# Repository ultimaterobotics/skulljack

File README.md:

# skulljack
This is a non-contact, open source EEG headset. Project just went public, it isn't properly described and documented yet (although we already have a working prototype). Proper description, firmware and PC source code coming soon

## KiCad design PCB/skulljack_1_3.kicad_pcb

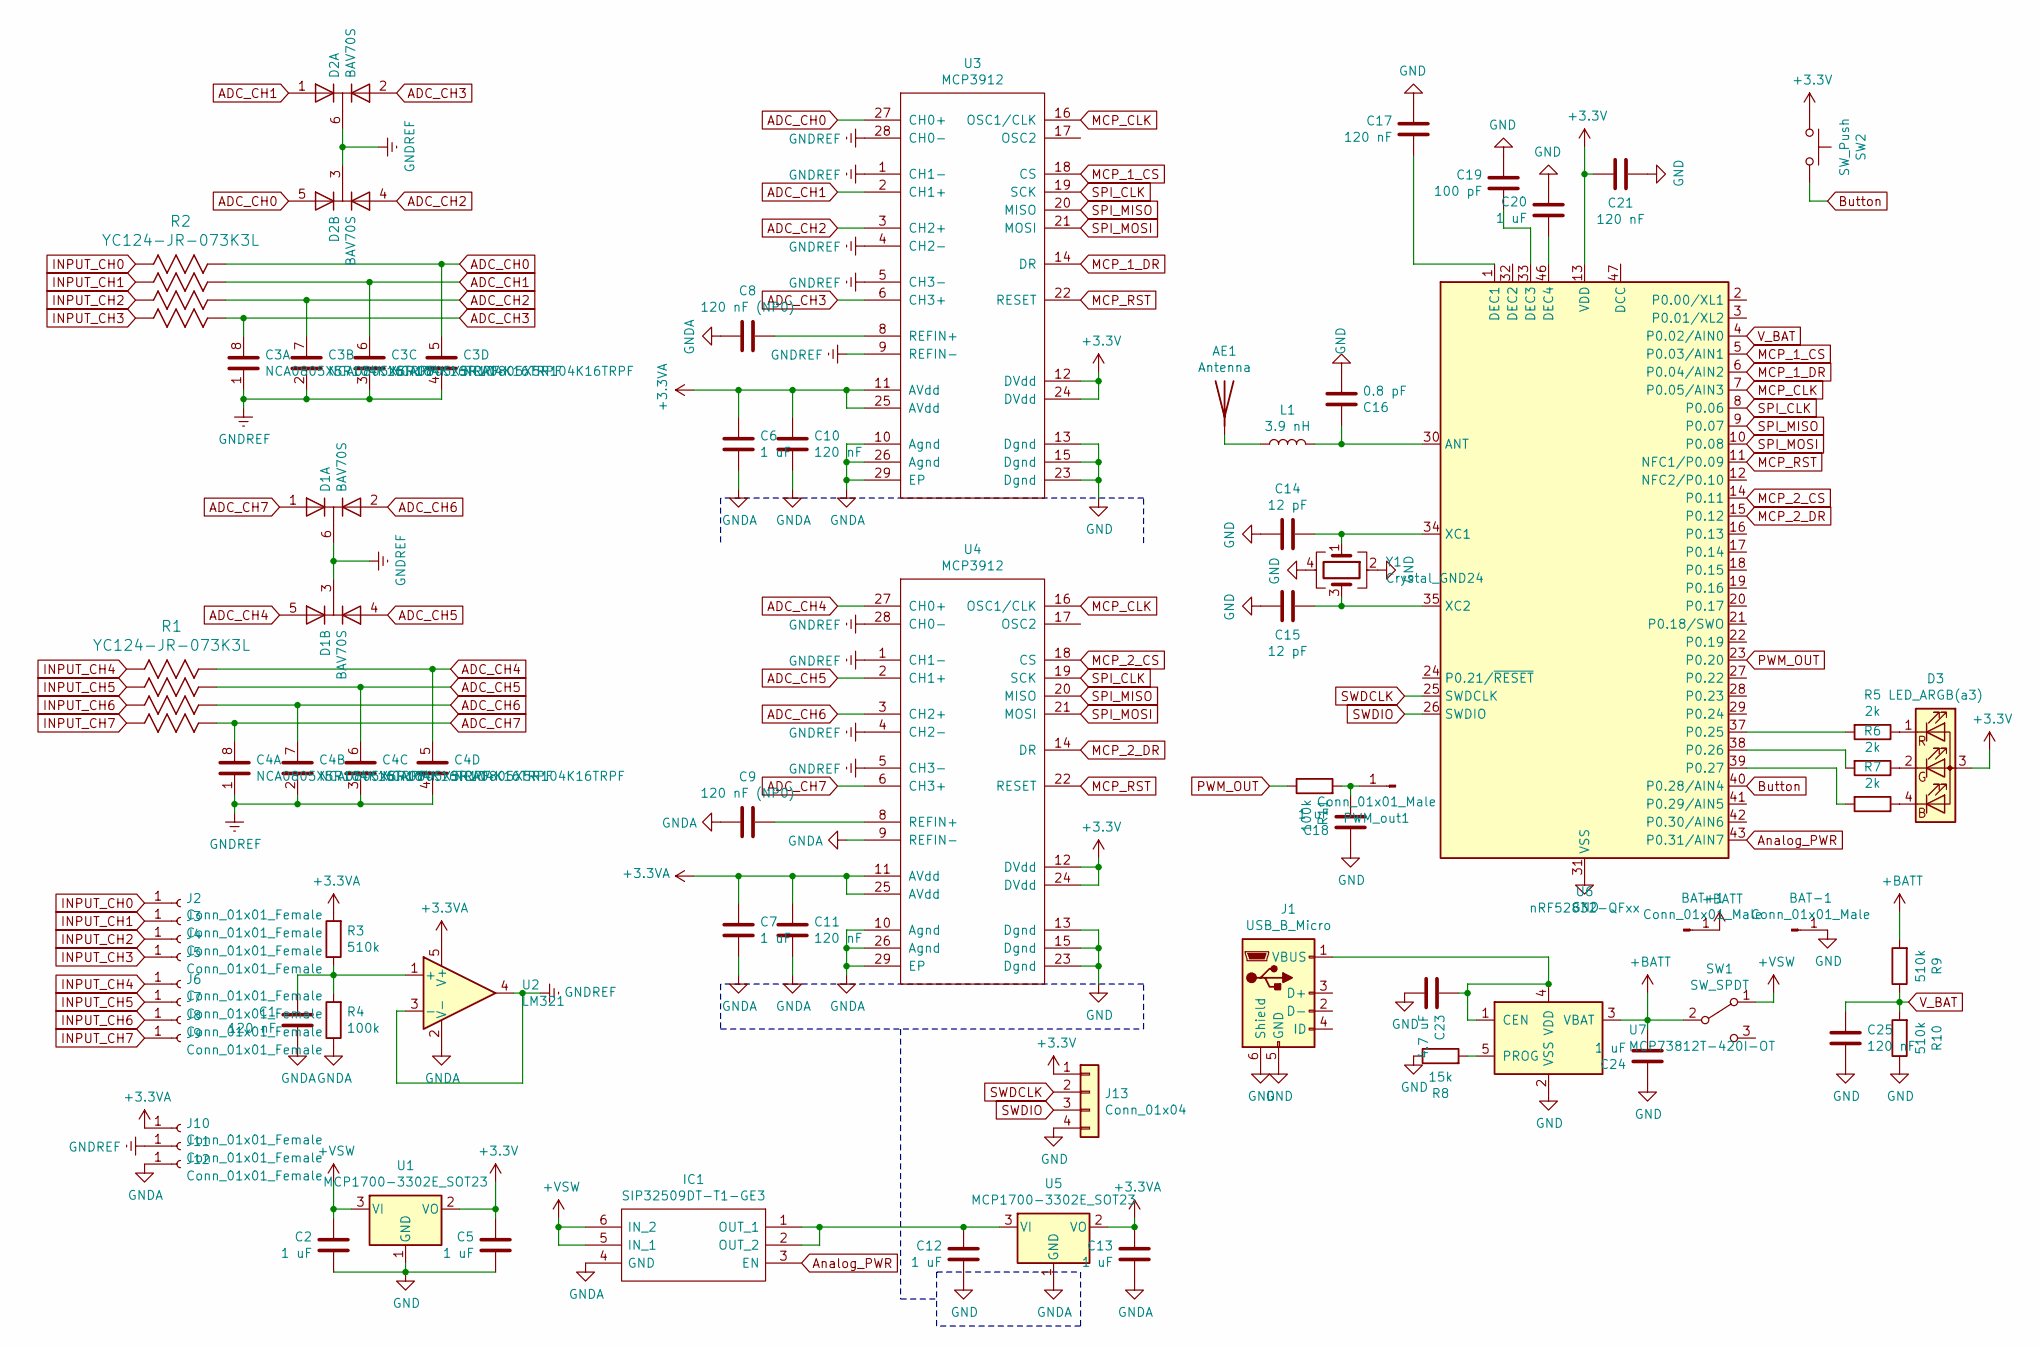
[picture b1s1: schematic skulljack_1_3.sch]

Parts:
AE1: Antenna; Texas_SWRA117D_2.4GHz_Right
BAT+1: Conn_01x01_Male; Pin_Header_Straight_1x01_Pitch2.54mm
BAT-1: Conn_01x01_Male; Pin_Header_Straight_1x01_Pitch2.54mm
C1, C10, C11, C17, C21, C25: 120 nF; C_0402_NoSilk
C2, C5, C6, C7, C12, C13, C18, C20, C24: 1 uF; C_0402_NoSilk
C3, C4: NCA0805X5R104K16TRPF; C_Array_4
C8, C9: 120 nF (NP0); C_0402_NoSilk
C14, C15: 12 pF; C_0402_NoSilk
C16: 0.8 pF; C_0402_NoSilk
C19: 100 pF; C_0402_NoSilk
C23: 4.7 uF; C_0402_NoSilk
D1, D2: BAV70S; SOT-363_SC-70-6
D3: LED_ARGB(a3); LED_RGB_0603
IC1: SIP32509DT-T1-GE3; SOT95P284X110-6N; Manufacturer_Part_Number SIP32509DT-T1-GE3
J1: USB_B_Micro; conn_usb_B_micro_smd_our
J2, J3, J4, J5, J6, J7, J8, J9, J10, J11, J12: Conn_01x01_Female; conn_06_20
J13: Conn_01x04; Pin_Header_Straight_1x04_Pitch2.54mm_SMD_Pin1Left
L1: 3.9 nH; L_0402
PWM_out1: Conn_01x01_Male; Pin_Header_Straight_1x01_Pitch2.54mm
R1, R2: YC124-JR-073K3L
R3, R9, R10: 510k; R_0402_NoSilk
R4, R11: 100k; R_0402_NoSilk
R5, R6, R7: 2k; R_0402_NoSilk
R8: 15k; R_0402_NoSilk
SW1: SW_SPDT; Slider_Switch_ali
SW2: SW_Push; SW_SPST_B3U-1000P
U1, U5: MCP1700-3302E_SOT23; SOT-23
U2: LM321; SOT-23-5
U3, U4: MCP3912; QFN-28-1EP_5x5mm_Pitch0.5mm
U6: nRF52832-QFxx; QFN-48-1EP_6x6mm_Pitch0.4mm_ThermalVias
U7: MCP73812T-420I-OT; SOT-23-5
Y1: Crystal_GND24; Crystal_SMD_2520-4pin_2.5x2.0mm

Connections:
+3.3VA: C6.1, C7.1, C10.1, C11.1, C13.2, J10.1, R3.2, U2.5 (V+), U3.11 (AVdd), U3.25 (AVdd), U4.11 (AVdd), U4.25 (AVdd), U5.2 (VO)
+3V3: C5.2, C21.2, D3.3 (A), J13.1, SW2.1, U1.2 (VO), U3.12 (DVdd), U3.24 (DVdd), U4.12 (DVdd), U4.24 (DVdd), U6.13 (VDD), U6.36 (VDD), U6.48 (VDD)
+BATT: BAT+1.1, C24.2, R9.2, SW1.2 (B), U7.3 (VBAT)
+VSW: C2.2, IC1.5 (IN_1), IC1.6 (IN_2), SW1.1 (A), U1.3 (VI)
ADC_CH0: C3.5, D2.5 (A), R2.8, U3.27 (CH0+)
ADC_CH1: C3.6, D2.1 (A), R2.7, U3.2 (CH1+)
ADC_CH2: C3.7, D2.4 (A), R2.6, U3.3 (CH2+)
ADC_CH3: C3.8, D2.2 (A), R2.5, U3.6 (CH3+)
ADC_CH4: C4.5, D1.5 (A), R1.8, U4.27 (CH0+)
ADC_CH5: C4.6, D1.4 (A), R1.7, U4.2 (CH1+)
ADC_CH6: C4.7, D1.2 (A), R1.6, U4.3 (CH2+)
ADC_CH7: C4.8, D1.1 (A), R1.5, U4.6 (CH3+)
Analog_PWR: IC1.3 (EN), U6.43 (P0.31/AIN7)
Button: SW2.2, U6.40 (P0.28/AIN4)
GND: AE1.2, BAT-1.1, C2.1, C5.1, C12.1, C14.2, C15.2, C16.1, C17.2, C18.1, C19.2, C20.2, C21.1, C23.2, C24.1, C25.2, J1.5 (GND), J1.6 (Shield), J13.4, R8.1, R10.1, U1.1 (GND), U3.13 (Dgnd), U3.15 (Dgnd), U3.23 (Dgnd), U4.13 (Dgnd), U4.15 (Dgnd), U4.23 (Dgnd), U6.31 (VSS), U6.45 (VSS), U6.49 (VSS), U7.2 (VSS), Y1.2, Y1.4
GNDA: C1.2, C6.2, C7.2, C8.2, C9.2, C10.2, C11.2, C13.1, IC1.4 (GND), J12.1, R4.1, U2.2 (V-), U3.10 (Agnd), U3.26 (Agnd), U3.29 (EP), U4.9 (REFIN-), U4.10 (Agnd), U4.26 (Agnd), U4.29 (EP), U5.1 (GND)
GNDREF: C3.1, C3.2, C3.3, C3.4, C4.1, C4.2, C4.3, C4.4, D1.3 (K), D1.6 (K), D2.3 (K), D2.6 (K), J11.1, U2.3 (-), U2.4, U3.1 (CH1-), U3.4 (CH2-), U3.5 (CH3-), U3.9 (REFIN-), U3.28 (CH0-), U4.1 (CH1-), U4.4 (CH2-), U4.5 (CH3-), U4.28 (CH0-)
INPUT_CH0: J2.1, R2.1
INPUT_CH1: J3.1, R2.2
INPUT_CH2: J4.1, R2.3
INPUT_CH3: J5.1, R2.4
INPUT_CH4: J6.1, R1.1
INPUT_CH5: J7.1, R1.2
INPUT_CH6: J8.1, R1.3
INPUT_CH7: J9.1, R1.4
MCP_1_CS: U3.18 (CS), U6.5 (P0.03/AIN1)
MCP_1_DR: U3.14 (DR), U6.6 (P0.04/AIN2)
MCP_2_CS: U4.18 (CS), U6.14 (P0.11)
MCP_2_DR: U4.14 (DR), U6.15 (P0.12)
MCP_CLK: U3.16 (OSC1/CLK), U4.16 (OSC1/CLK), U6.7 (P0.05/AIN3)
MCP_RST: U3.22 (RESET), U4.22 (RESET), U6.11 (NFC1/P0.09)
unnamed: AE1.1, L1.1
unnamed: C1.1, R3.1, R4.2, U2.1 (+)
unnamed: C8.1, U3.8 (REFIN+)
unnamed: C9.1, U4.8 (REFIN+)
unnamed: C12.2, IC1.1 (OUT_1), IC1.2 (OUT_2), U5.3 (VI)
unnamed: C14.1, U6.34 (XC1), Y1.1
unnamed: C15.1, U6.35 (XC2), Y1.3
unnamed: C16.2, L1.2, U6.30 (ANT)
unnamed: C17.1, U6.1 (DEC1)
unnamed: C18.2, PWM_out1.1, R11.2
unnamed: C19.1, U6.33 (DEC3)
unnamed: C20.1, U6.46 (DEC4)
unnamed: C23.1, J1.1 (VBUS), U7.1 (CEN), U7.4 (VDD)
unnamed: D3.1 (RK), R5.1
unnamed: D3.2 (GK), R6.1
unnamed: D3.4 (BK), R7.1
unnamed: R5.2, U6.37 (P0.25)
unnamed: R6.2, U6.38 (P0.26)
unnamed: R7.2, U6.39 (P0.27)
unnamed: R8.2, U7.5 (PROG)
PWM_OUT: R11.1, U6.23 (P0.20)
SPI_CLK: U3.19 (SCK), U4.19 (SCK), U6.8 (P0.06)
SPI_MISO: U3.20 (MISO), U4.20 (MISO), U6.9 (P0.07)
SPI_MOSI: U3.21 (MOSI), U4.21 (MOSI), U6.10 (P0.08)
SWDCLK: J13.2, U6.25 (SWDCLK)
SWDIO: J13.3, U6.26 (SWDIO)
V_BAT: C25.1, R9.1, R10.2, U6.4 (P0.02/AIN0)

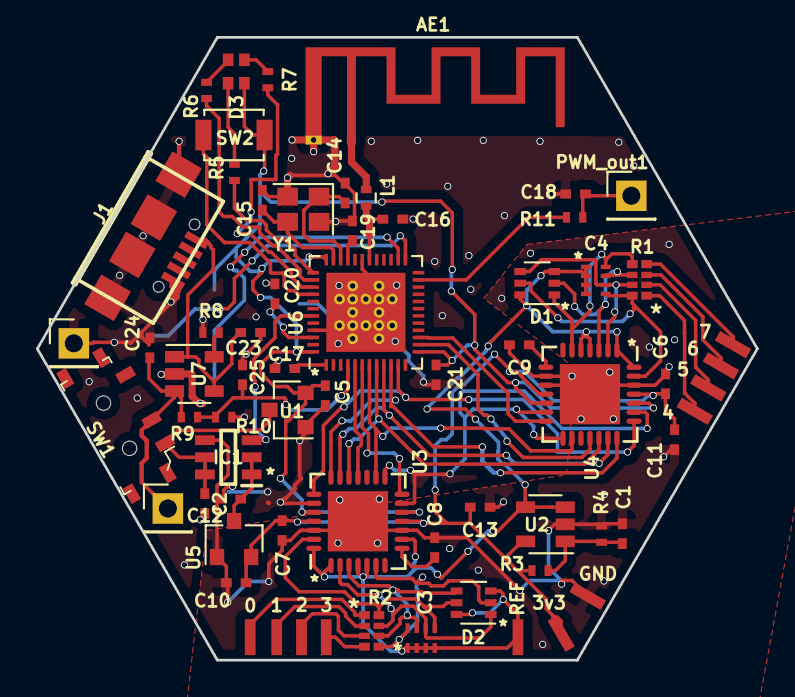
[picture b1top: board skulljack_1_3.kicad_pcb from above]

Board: 2 copper layers, 40.0 x 34.6 mm, 67 parts (1 on the bottom side), 58 nets.

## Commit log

2019-05-13 pcb initial commit

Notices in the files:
parts and their libraries:
Copyright 2016 Accelerated Designs. All rights reserved.
